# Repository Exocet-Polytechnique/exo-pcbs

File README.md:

# Cockpit
* 3 entrées GPIO (boutons)
* 3 sorties GPIO (DEL d'état)

#### Boutons

I = V/R

I = 3.3 / 10 000 = 0.33 mA

Utiliser un connecteur **JST ZH** (compact, facile à manipuler)

#### Del d'états

R = V / I = 3.3 - V<sub>D</sub> / 0.01

V<sub>D</sub> : Chute de tension directe (i.e. tension minimale requise pour que le courant commence à circuler à travers un composant électronique). Pour une DEL rouge ou verte, V<sub>D</sub> = 2 V.

I = 10 mA (Assez de courant pour faire briller une DEL)

R = 3.3 - 2 / 0.01 = 130 Ω

Utiliser un connecteur **JST GH** (plus compact, mais un peu compliqué à manipuler)

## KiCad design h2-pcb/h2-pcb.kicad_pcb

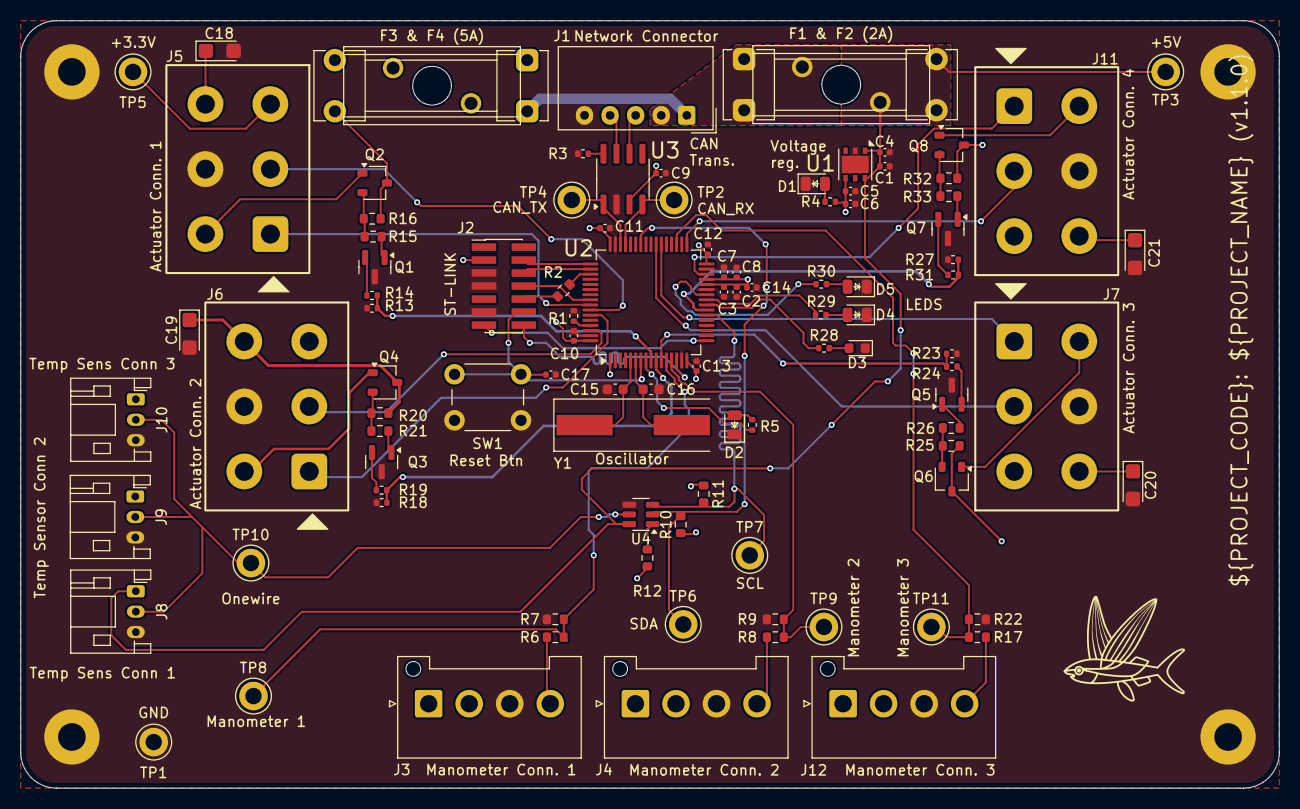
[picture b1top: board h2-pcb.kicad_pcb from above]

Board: 2 copper layers, 123.0 x 75.0 mm, 104 parts (0 on the bottom side), 69 nets.

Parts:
C1, C3, C6, C9, C10, C11, C12, C13, C17: 100n; C_0402_1005Metric
C2, C4, C5, C8: 1u; C_0402_1005Metric
C7: 10n; C_0402_1005Metric
C14: 4.7u; C_0402_1005Metric
C15, C16: 30p; C_0603_1608Metric
C18, C19, C20, C21: 10u; CP_EIA-3216-18_Kemet-A
D1, D4: GREEN; LED_0805_2012Metric_With_Annotations
D2, D5: YELLOW; LED_0805_2012Metric_With_Annotations
D3: RED; LED_0603_1608Metric
F1: 2A; Fuse_Holder_Littelfuse_01530008
F2: 2A; Fuseholder_Clip-5x20mm_Littelfuse_111_Lateral_P18.80x5.00mm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
F3: 5A; Fuse_Holder_Littelfuse_01530008
F4: 5A; Fuseholder_Clip-5x20mm_Littelfuse_111_Lateral_P18.80x5.00mm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
H1, H2, H3, H4: 2.7mm; MountingHole_2.7mm_Pad
J1: Network Connector; Molex_SPOX_5268-05A_1x05_P2.50mm_Horizontal
J2: STDC14; PinHeader_2x07_P1.27mm_Vertical_SMD
J3: Manometer Connector 1; JST_VH_B4P-VH-FB-B_1x04_P3.96mm_Vertical
J4: Manometer Connector 2; JST_VH_B4P-VH-FB-B_1x04_P3.96mm_Vertical
J5: Actuator Connector 1; TE_UNIVERSAL-MNL_6Pin_Horizontal_PCB_Header
J6: Actuator Connector 2; TE_UNIVERSAL-MNL_6Pin_Horizontal_PCB_Header
J7: Actuator Connector 3; TE_UNIVERSAL-MNL_6Pin_Horizontal_PCB_Header
J8: Temp Sensor Conn 1; JST_PH_S3B-PH-K_1x03_P2.00mm_Horizontal
J9: Temp Sensor Conn 2; JST_PH_S3B-PH-K_1x03_P2.00mm_Horizontal
J10: Temp Sensor Conn 3; JST_PH_S3B-PH-K_1x03_P2.00mm_Horizontal
J11: Actuator Connector 4; TE_UNIVERSAL-MNL_6Pin_Horizontal_PCB_Header
J12: Manometer Connector 3; JST_VH_B4P-VH-FB-B_1x04_P3.96mm_Vertical
Q1, Q3, Q5, Q7: NMOS; SOT-23
Q2, Q4, Q6, Q8: PMOS; SOT-23W
R1, R3, R13, R18, R23, R27: 10k; R_0402_1005Metric
R2: 47; R_0603_1608Metric
R4, R5, R28, R29, R30: 1k; R_0402_1005Metric
R6, R8, R17: 3.6k; R_0603_1608Metric
R7, R9, R10, R11, R12, R22: 6.8k; R_0603_1608Metric
R14, R19, R24, R31: 100; R_0402_1005Metric
R15, R21, R26, R33: 7.5k; R_0603_1608Metric
R16, R20, R25, R32: 4.7k; R_0603_1608Metric
SW1: SW_Push; SW_PUSH_6mm
TP1, TP2, TP3, TP4, TP5, TP6, TP7, TP8, TP9, TP10, TP11: TestPoint; TestPoint_Keystone_5005-5009_Compact
U1: LD39050PU33R; DFN-6-1EP_3x3mm_P0.95mm_EP1.7x2.6mm
U2: STM32G474RBT6; LQFP-64_10x10mm_P0.5mm
U3: SN65HVD230; SOIC-8_3.9x4.9mm_P1.27mm
U4: DS2484R; SOT-23-6
Y1: 8MHz; Crystal_SMD_HC49-SD

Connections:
+3.3V: C2.2, C3.2, C5.1, C6.1, C7.1, C8.1, C9.1, C10.1, C11.1, C12.1, C13.1, C14.1, J2.3 (VCC), J5.3, J6.3, J7.3, J11.3, R4.1, R10.1, R11.1, R12.1, TP5.1, U1.4 (V_{out}), U2.1 (VBAT), U2.16 (VDD), U2.28 (VREF+), U2.29 (VDDA), U2.32 (VDD), U2.48 (VDD), U2.64 (VDD), U3.3 (VCC)
+5V: C1.1, C4.1, F1.2, F2.2, J8.1, J9.1, J10.1, TP3.1, U1.1 (EN), U1.6 (V_{in}), U4.6 (V_{CC})
+24V: C18.1, C19.1, C20.1, C21.1, F3.2, F4.2, J3.1, J4.1, J5.6, J6.6, J7.6, J11.6, J12.1, Q2.3 (S), Q4.3 (S), Q6.3 (S), Q8.3 (S), R16.1, R20.1, R25.1, R32.1
/ACTUATOR_CTRL1: J5.4, Q2.1 (D)
/ACTUATOR_CTRL2: J6.4, Q4.1 (D)
/ACTUATOR_CTRL3: J7.4, Q6.1 (D)
/ACTUATOR_CTRL4: J11.4, Q8.1 (D)
/ACTUATOR_GPIO1: R13.1, R14.1, U2.9 (PC1)
/ACTUATOR_GPIO2: R18.1, R19.1, U2.10 (PC2)
/ACTUATOR_GPIO3: R23.1, R24.1, U2.11 (PC3)
/ACTUATOR_GPIO4: R27.1, R31.1, U2.23 (PC5)
/LED_1: R28.1, U2.24 (PB0)
/LED_2: R29.1, U2.25 (PB1)
/LED_3: R30.1, U2.26 (PB2)
/MANOMETER_1: R6.2, R7.1, TP8.1, U2.12 (ADC1_IN1)
/MANOMETER_2: R8.2, R9.1, TP9.1, U2.13 (ADC2_IN2)
/MANOMETER_3: R17.2, R22.1, TP11.1, U2.35 (ADC3_IN5)
/NC_1: J5.2, U2.58 (PB5)
/NC_2: J6.2, U2.62 (PB9)
/NC_3: J7.2, U2.39 (PC7)
/NC_4: J11.2, U2.33 (PB11)
/NO_1: J5.1, U2.57 (PB4)
/NO_2: J6.1, U2.59 (PB6)
/NO_3: J7.1, U2.38 (PC6)
/NO_4: J11.1, U2.30 (PB10)
/ONEWIRE: J8.2, J9.2, J10.2, TP10.1, U4.5 (IO)
/SCL_TEMP: R11.2, TP7.1, U2.22 (I2C2_SCL), U4.3 (SCL)
/SDA_TEMP: R10.2, TP6.1, U2.42 (I2C2_SDA), U4.2 (SDA)
/STM32 Base Layout/CAN_H: J1.4 (CAN_H), U3.7 (CANH)
/STM32 Base Layout/CAN_L: J1.3 (CAN_L), U3.6 (CANL)
/STM32 Base Layout/CAN_RX: TP2.1, U2.45 (FDCAN1_RX), U3.4 (R)
/STM32 Base Layout/CAN_TX: TP4.1, U2.46 (FDCAN1_TX), U3.1 (D)
/STM32 Base Layout/OSC_IN: C15.1, U2.5 (RCC_OSC_IN), Y1.1
/STM32 Base Layout/OSC_OUT: C16.1, U2.6 (RCC_OSC_OUT), Y1.2
/STM32 Base Layout/STATUS_LED: R5.1, U2.8 (PC0)
/STM32 Base Layout/T_JCLK/T_SWCLK: J2.6 (JCLK/SWCLK), U2.50 (SYS_JTCK-SWCLK)
/STM32 Base Layout/T_JTDI: J2.10 (JTDI/NC), R2.2
/STM32 Base Layout/T_JTDO/T_SWO: J2.8 (JTDO/SWO), U2.56 (SYS_JTDO-SWO)
/STM32 Base Layout/T_JTMS/T_SWDIO: J2.4 (JTMS/SWDIO), U2.49 (SYS_JTMS-SWDIO)
/STM32 Base Layout/T_NRST: C17.2, J2.12 (~RST), SW1.1, U2.7 (PG10)
/STM32 Base Layout/T_VCP_RX: J2.13 (VCP_RX), U2.17 (LPUART1_RX)
/STM32 Base Layout/T_VCP_TX: J2.14 (VCP_TX), U2.14 (LPUART1_TX)
GND: C1.2, C2.1, C3.1, C4.2, C5.2, C6.2, C7.2, C8.2, C9.2, C10.2, C11.2, C12.2, C13.2, C14.2, C15.2, C16.2, C17.1, C18.2, C19.2, C20.2, C21.2, D1.1 (K), D2.1 (K), D3.1 (K), D4.1 (K), D5.1 (K), H1.1, H2.1, H3.1, H4.1, J1.5 (GND), J2.5 (GND), J2.7 (GND), J2.11 (GNDDetect), J3.3, J4.3, J5.5, J6.5, J7.5, J8.3, J9.3, J10.3, J11.5, J12.3, Q1.3 (S), Q3.3 (S), Q5.3 (S), Q7.3 (S), R1.2, R3.2, R7.2, R9.2, R13.2, R18.2, R22.2, R23.2, R27.2, SW1.2, TP1.1, U1.2 (GND), U1.7 (GND), U2.15 (VSS), U2.27 (VSSA), U2.31 (VSS), U2.47 (VSS), U2.63 (VSS), U3.2 (GND), U4.4 (GND)
unnamed: D1.2 (A), R4.2
unnamed: D2.2 (A), R5.2
unnamed: D3.2 (A), R28.2
unnamed: D4.2 (A), R29.2
unnamed: D5.2 (A), R30.2
unnamed: F1.1, F2.1, J1.2 (+5V)
unnamed: F3.1, F4.1, J1.1 (+24V)
unnamed: J3.4, R6.1
unnamed: J4.4, R8.1
unnamed: J12.4, R17.1
unnamed: Q1.1 (D), R15.2
unnamed: Q1.2 (G), R14.2
unnamed: Q2.2 (G), R15.1, R16.2
unnamed: Q3.1 (D), R21.2
unnamed: Q3.2 (G), R19.2
unnamed: Q4.2 (G), R20.2, R21.1
unnamed: Q5.1 (D), R26.2
unnamed: Q5.2 (G), R24.2
unnamed: Q6.2 (G), R25.2, R26.1
unnamed: Q7.1 (D), R33.2
unnamed: Q7.2 (G), R31.2
unnamed: Q8.2 (G), R32.2, R33.1
unnamed: R2.1, U2.51 (SYS_JTDI)
unnamed: R1.1, U2.61 (PB8)
unnamed: R3.1, U3.8 (Rs)
unnamed: R12.2, U4.1 (~SLPZ)

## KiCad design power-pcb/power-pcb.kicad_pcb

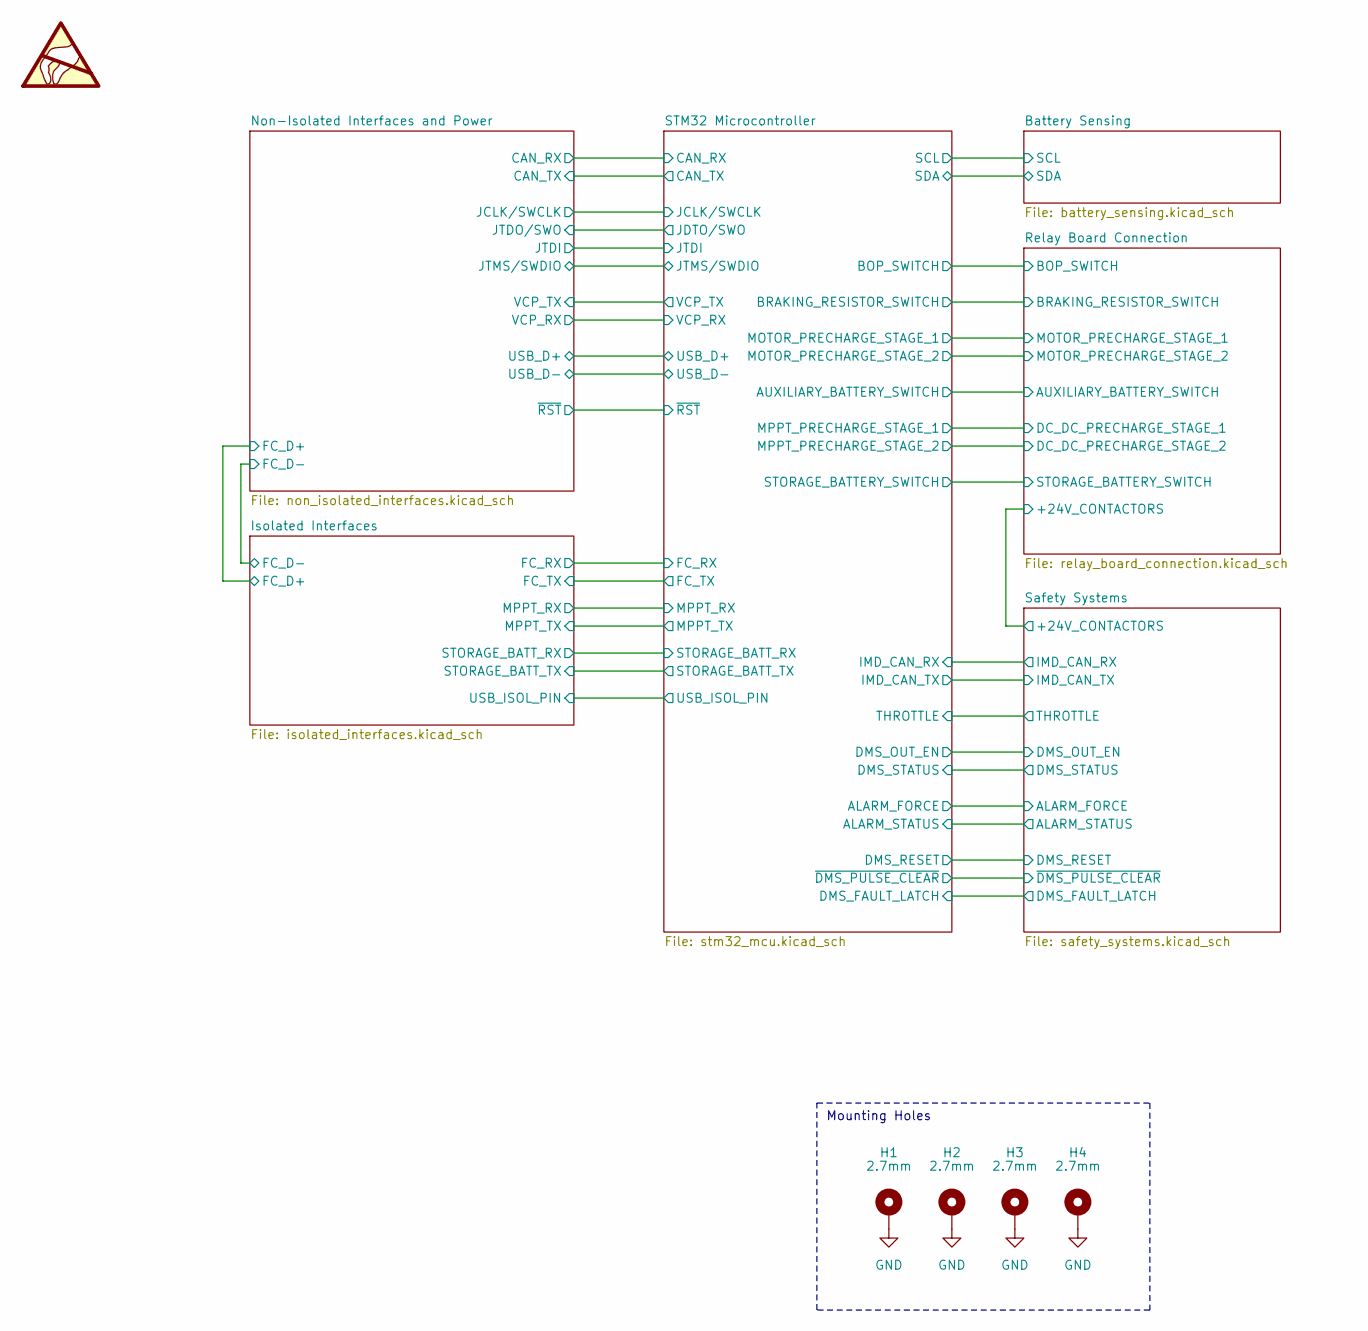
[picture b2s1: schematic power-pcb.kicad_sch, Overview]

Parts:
H1, H2, H3, H4: 2.7mm; MountingHole_2.7mm_Pad
SYM1: SYM_ESD_Large; ESD-Logo_8.9x8mm_SilkScreen

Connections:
GND: H1.1 (1_1), H2.1 (1_1), H3.1 (1_1), H4.1 (1_1); also elsewhere on the board

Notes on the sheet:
Mounting Holes

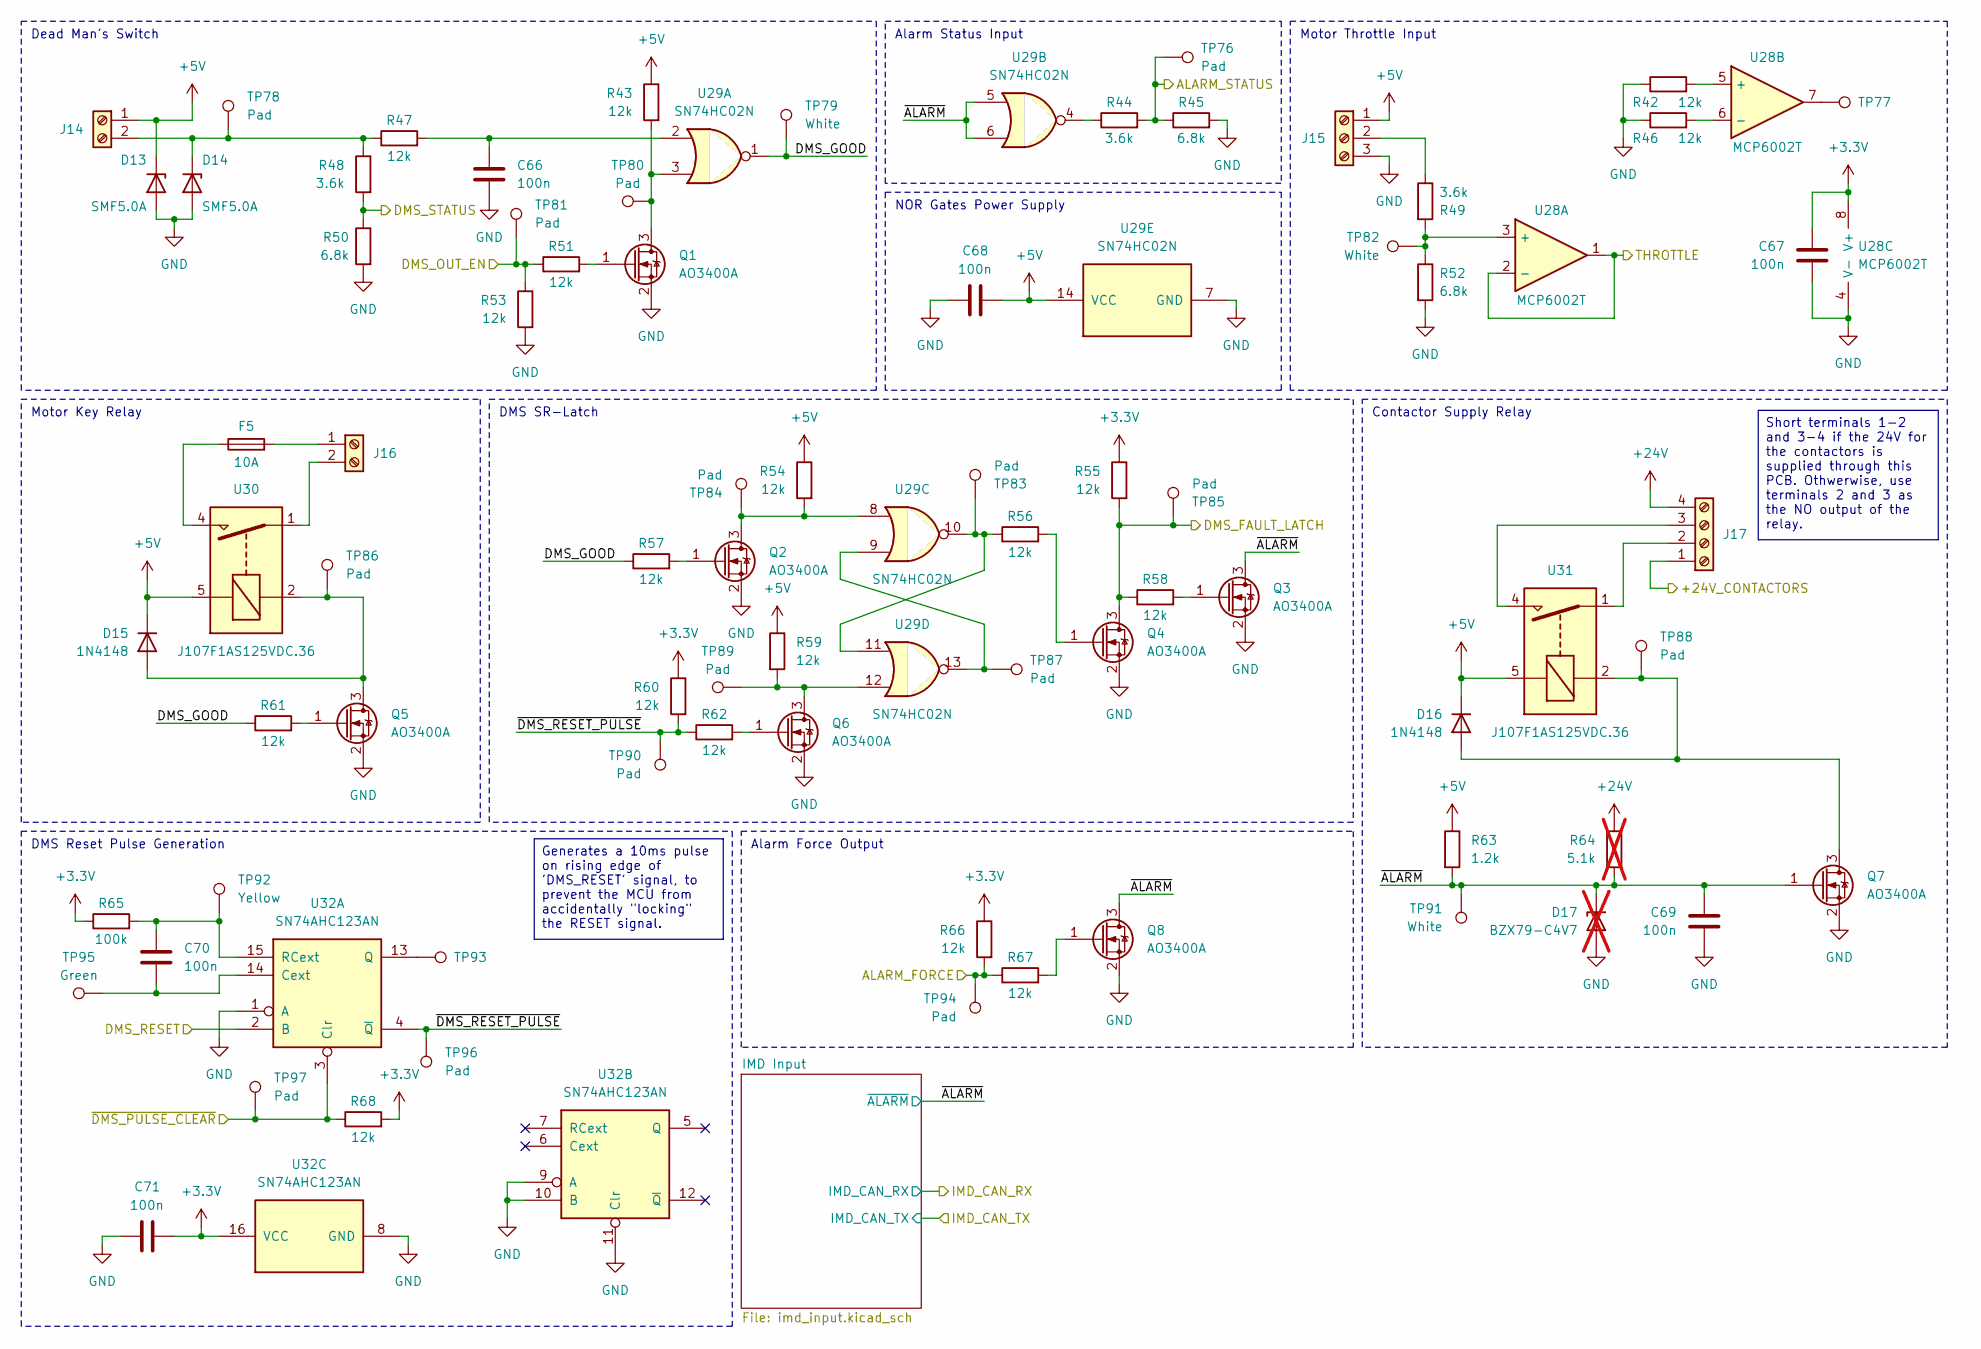
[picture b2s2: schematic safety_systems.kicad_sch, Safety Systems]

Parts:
C66, C67, C68, C69, C70, C71: 100n; C_0402_1005Metric_Pad0.74x0.62mm_HandSolder; JLCPCB C307331
D13, D14: SMF5.0A; D_SOD-123F; JLCPCB C19077497
D15, D16: 1N4148; D_DO-35_SOD27_P7.62mm_Horizontal; MPN 1N4148
D17: BZX79-C4V7; D_DO-35_SOD27_P7.62mm_Horizontal; MPN BZX79-C4V7,133; not fitted
F5: 10A; Fuseholder_Littelfuse_Combined; MPN 01110501Z
J14, J16: Screw_Terminal_01x02; Wuerth_Term_Blk_2pos_Side_Entry_5mm; MPN 691137710002
J15: Screw_Terminal_01x03; Wuerth_Term_Blk_3pos_Side_Entry_5mm; MPN 691137710003
J17: Screw_Terminal_01x04; Wuerth_Term_Blk_4pos_Side_Entry_5mm; MPN 691137710004
Q1, Q2, Q3, Q4, Q5, Q6, Q7, Q8: AO3400A; SOT-23_Handsoldering; MPN AO3400A; JLCPCB C20917
R42, R43, R46, R47, R51, R53, R54, R55, R56, R57, R58, R59, R60, R61, R62, R66, R67, R68: 12k; R_0402_1005Metric_Pad0.72x0.64mm_HandSolder; JLCPCB C25752
R44, R48, R49: 3.6k; R_0603_1608Metric_Pad0.98x0.95mm_HandSolder; JLCPCB C22980
R45, R50, R52: 6.8k; R_0603_1608Metric_Pad0.98x0.95mm_HandSolder; JLCPCB C23212
R63: 1.2k; R_0603_1608Metric_Pad0.98x0.95mm_HandSolder; JLCPCB C22765
R64: 5.1k; R_0402_1005Metric_Pad0.72x0.64mm_HandSolder; JLCPCB C25905; not fitted
R65: 100k; R_0603_1608Metric_Pad0.98x0.95mm_HandSolder; JLCPCB C25803
TP76, TP78, TP80, TP81, TP83, TP84, TP85, TP86, TP87, TP88, TP89, TP90, TP94, TP96, TP97: Pad; TestPoint_Pad_D1.5mm
TP77, TP93: Hole; TestPoint_THTPad_D2.0mm_Drill1.0mm
TP79, TP82, TP91: White; TestPoint_Keystone_5005-5009_Compact; MPN 5007
TP92: Yellow; TestPoint_Keystone_5005-5009_Compact; MPN 5009
TP95: Green; TestPoint_Keystone_5005-5009_Compact; MPN 5121
U28: MCP6002T; SOIC-8_3.9x4.9mm_P1.27mm; MPN MCP6002T-I/SN; JLCPCB C7377
U29: SN74HC02N; DIP-14_W7.62mm_LongPads; MPN SN74HC02N
U30, U31: J107F1AS125VDC.36; Relay_SPDT_Omron-G5LE-1; MPN J107F1AS125VDC.36
U32: SN74AHC123AN; DIP-16_W7.62mm_LongPads; MPN SN74AHC123AN

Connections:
+3.3V: C67.1, C71.2, R55.1, R60.1, R65.1, R66.1, R68.2, U28.8 (V+), U32.16 (VCC); also elsewhere on the board
+5V: C68.2, D13.1 (K), D15.1 (K), D16.1 (K), J14.1, J15.1, R43.1, R54.1, R59.1, R63.1, U29.14 (VCC), U30.5, U31.5; also elsewhere on the board
+24V: J17.4, R64.1; also elsewhere on the board
/Relay Board Connection/+24V_CONTACTORS: J17.1; also elsewhere on the board
/STM32 Microcontroller/ALARM_FORCE: R66.2, R67.1, TP94.1 (1_1); also elsewhere on the board
/STM32 Microcontroller/ALARM_STATUS: R44.2, R45.1, TP76.1 (1_1); also elsewhere on the board
/STM32 Microcontroller/DMS_FAULT_LATCH: Q4.3 (D), R55.2, R58.1, TP85.1 (1_1); also elsewhere on the board
/STM32 Microcontroller/DMS_OUT_EN: R51.1, R53.1, TP81.1 (1_1); also elsewhere on the board
/STM32 Microcontroller/DMS_RESET: U32.2 (B); also elsewhere on the board
/STM32 Microcontroller/DMS_STATUS: R48.2, R50.1; also elsewhere on the board
/STM32 Microcontroller/THROTTLE: U28.1, U28.2 (-); also elsewhere on the board
/STM32 Microcontroller/~DMS_PULSE_CLEAR: R68.1, TP97.1 (1_1), U32.3 (Clr); also elsewhere on the board
/Safety Systems/DMS_GOOD: R57.1, R61.1, TP79.1 (1_1), U29.1
/Safety Systems/~ALARM: C69.1, D17.1 (K), Q3.3 (D), Q7.1 (G), Q8.3 (D), R63.2, R64.2, TP91.1 (1_1), U29.5, U29.6; also elsewhere on the board
/Safety Systems/~DMS_RESET_PULSE: R60.2, R62.1, TP90.1 (1_1), TP96.1 (1_1), U32.4 (~Q)
GND: C66.2, C67.2, C68.1, C69.2, C71.1, D13.2 (A), D14.2 (A), D17.2 (A), J15.3, Q1.2 (S), Q2.2 (S), Q3.2 (S), Q4.2 (S), Q5.2 (S), Q6.2 (S), Q7.2 (S), Q8.2 (S), R42.1, R45.2, R46.1, R50.2, R52.2, R53.2, U28.4 (V-), U29.7 (GND), U32.1 (A), U32.8 (GND), U32.9 (A), U32.10 (B), U32.11 (Clr); also elsewhere on the board
unnamed: C66.1, R47.2, U29.2
unnamed: D14.1 (K), J14.2, R47.1, R48.1, TP78.1 (1_1)
unnamed: D15.2 (A), Q5.3 (D), TP86.1 (1_1), U30.2
unnamed: D16.2 (A), Q7.3 (D), TP88.1 (1_1), U31.2
unnamed: F5.1, U30.4
unnamed: J15.2, R49.1
unnamed: F5.2, J16.1
unnamed: J16.2, U30.1
unnamed: J17.2, U31.1
unnamed: J17.3, U31.4
unnamed: Q1.3 (D), R43.2, TP80.1 (1_1), U29.3
unnamed: Q1.1 (G), R51.2
unnamed: Q2.3 (D), R54.2, TP84.1 (1_1), U29.8
unnamed: Q2.1 (G), R57.2
unnamed: Q3.1 (G), R58.2
unnamed: Q4.1 (G), R56.2
unnamed: Q5.1 (G), R61.2
unnamed: Q6.3 (D), R59.2, TP89.1 (1_1), U29.12
unnamed: Q6.1 (G), R62.2
unnamed: Q8.1 (G), R67.2
unnamed: R44.1, U29.4
unnamed: R56.1, TP83.1 (1_1), U29.10, U29.11
unnamed: TP77.1 (1_1), U28.7
unnamed: TP87.1 (1_1), U29.9, U29.13
unnamed: R49.2, R52.1, TP82.1 (1_1), U28.3 (+)
unnamed: R42.2, U28.5 (+)
unnamed: R46.2, U28.6 (-)
unnamed: C70.2, TP95.1 (1_1), U32.14 (Cext)
unnamed: TP93.1 (1_1), U32.13 (Q)
unnamed: C70.1, R65.2, TP92.1 (1_1), U32.15 (RCext)

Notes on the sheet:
DMS SR-Latch
Motor Key Relay
DMS Reset Pulse Generation
Dead Man's Switch
Motor Throttle Input
NOR Gates Power Supply
Contactor Supply Relay
Alarm Status Input
Alarm Force Output
Short terminals 1-2 and 3-4 if the 24V for the contactors is supplied through this PCB. Othwerwise, use terminals 2 and 3 as the NO output of the relay.
Generates a 10ms pulse on rising edge of 'DMS_RESET' signal, to prevent the MCU from accidentally "locking" the RESET signal.

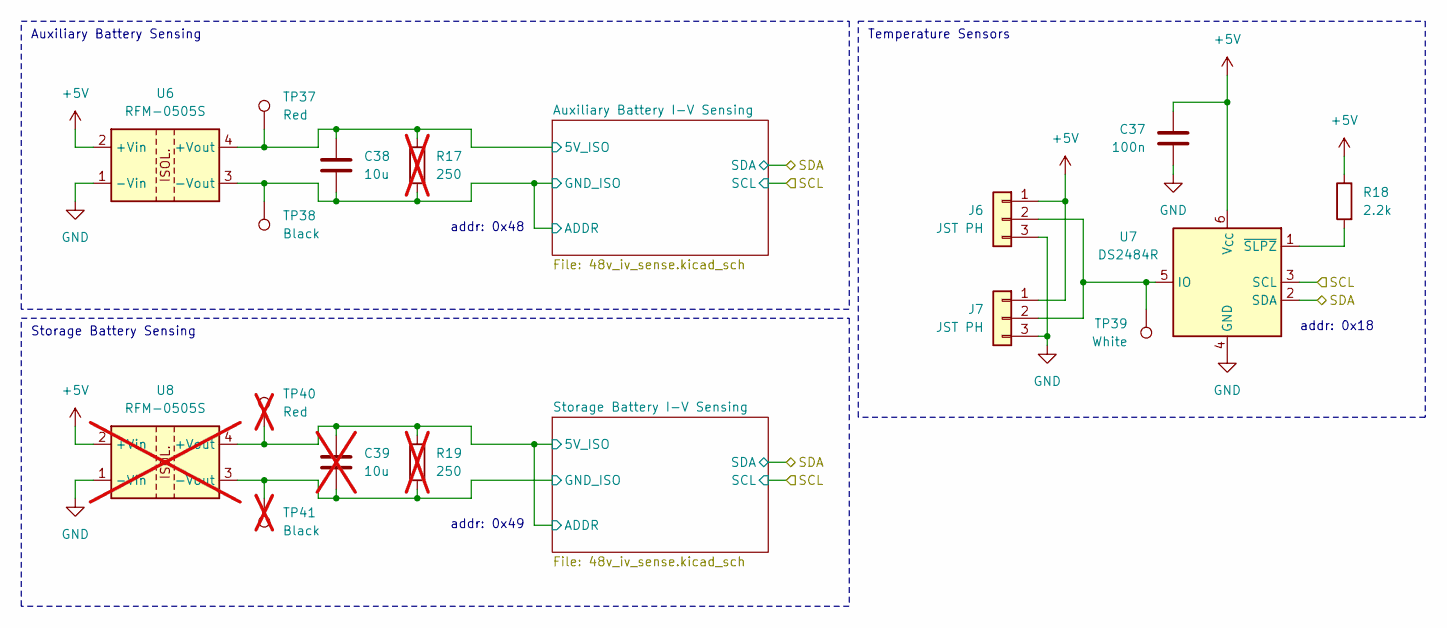
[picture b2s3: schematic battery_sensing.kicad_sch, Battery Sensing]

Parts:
C37: 100n; C_0402_1005Metric_Pad0.74x0.62mm_HandSolder; JLCPCB C307331
C38: 10u; C_1206_3216Metric_Pad1.33x1.80mm_HandSolder; JLCPCB C13585
C39: 10u; C_1206_3216Metric_Pad1.33x1.80mm_HandSolder; JLCPCB C13585; not fitted
J6, J7: JST PH; JST_PH_S3B-PH-K_1x03_P2.00mm_Horizontal; MPN S3B-PH-K-S
R17, R19: 250; R_Axial_DIN0309_L9.0mm_D3.2mm_P12.70mm_Horizontal; MPN MFR-25FTE52-270R; not fitted
R18: 2.2k; R_0603_1608Metric_Pad0.98x0.95mm_HandSolder; JLCPCB C4190
TP37: Red; TestPoint_Keystone_5005-5009_Compact; MPN 5005
TP38: Black; TestPoint_Keystone_5005-5009_Compact; MPN 5006
TP39: White; TestPoint_Keystone_5005-5009_Compact; MPN 5007
TP40: Red; TestPoint_Keystone_5005-5009_Compact; MPN 5005; not fitted
TP41: Black; TestPoint_Keystone_5005-5009_Compact; MPN 5006; not fitted
U6: RFM-0505S; RECOM_SIP-4; MPN RFM-0505S
U7: DS2484R; SOT-23-6; JLCPCB C124886
U8: RFM-0505S; RECOM_SIP-4; MPN RFM-0505S; not fitted

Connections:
+5V: C37.1, J6.1, J7.1, R18.1, U6.2 (+Vin), U7.6 (V_{CC}), U8.2 (+Vin); also elsewhere on the board
/Battery Sensing/Auxiliary Battery I-V Sensing/5V_ISO: C38.1, R17.1, TP37.1 (1_1), U6.4 (+Vout); also elsewhere on the board
/Battery Sensing/Auxiliary Battery I-V Sensing/ADDR: C38.2, R17.2, TP38.1 (1_1), U6.3 (-Vout); also elsewhere on the board
/Battery Sensing/SCL: U7.3 (SCL); also elsewhere on the board
/Battery Sensing/SDA: U7.2 (SDA); also elsewhere on the board
/Battery Sensing/Storage Battery I-V Sensing/5V_ISO: C39.1, R19.1, TP40.1 (1_1), U8.4 (+Vout); also elsewhere on the board
/Battery Sensing/Storage Battery I-V Sensing/GND_ISO: C39.2, R19.2, TP41.1 (1_1), U8.3 (-Vout); also elsewhere on the board
GND: C37.2, J6.3, J7.3, U6.1 (-Vin), U7.4 (GND), U8.1 (-Vin); also elsewhere on the board
unnamed: J6.2, J7.2, TP39.1 (1_1), U7.5 (IO)
unnamed: R18.2, U7.1 (~SLPZ)

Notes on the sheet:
Temperature Sensors
addr: 0x18
Auxiliary Battery Sensing
Storage Battery Sensing
addr: 0x49
addr: 0x48

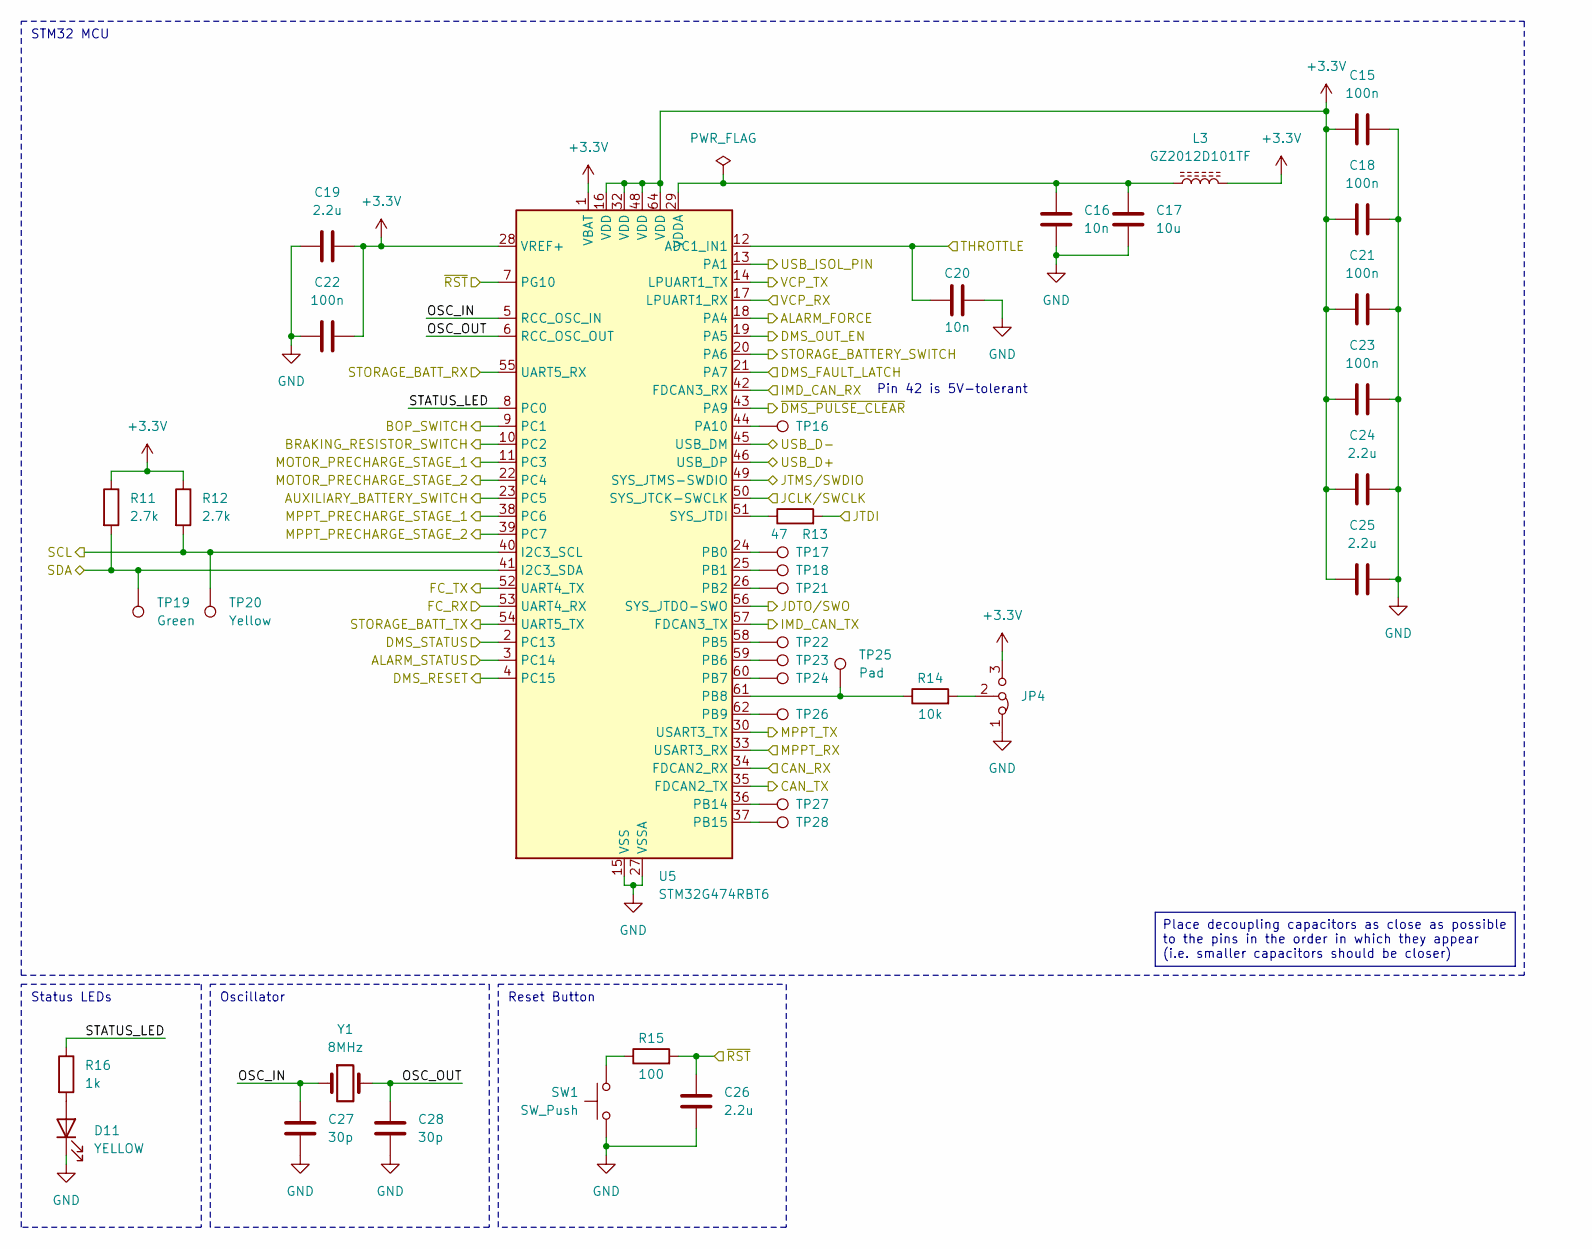
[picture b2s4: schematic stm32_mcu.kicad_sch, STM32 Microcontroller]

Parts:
C15, C18, C21, C22, C23: 100n; C_0402_1005Metric_Pad0.74x0.62mm_HandSolder; JLCPCB C307331
C16, C20: 10n; C_0402_1005Metric_Pad0.74x0.62mm_HandSolder; JLCPCB C15195
C17: 10u; C_1206_3216Metric_Pad1.33x1.80mm_HandSolder; JLCPCB C13585
C19, C24, C25, C26: 2.2u; C_0805_2012Metric_Pad1.18x1.45mm_HandSolder; JLCPCB C377773
C27, C28: 30p; C_0603_1608Metric_Pad1.08x0.95mm_HandSolder; JLCPCB C1658
D11: YELLOW; LED_0805_2012Metric_With_Annotations; JLCPCB C2296
JP4: Jumper_3_Bridged12; PinHeader_1x03_P2.54mm_Vertical; MPN PR20203VBNN
L3: GZ2012D101TF; L_0805_2012Metric_Pad1.05x1.20mm_HandSolder; JLCPCB C1015
R11, R12: 2.7k; R_0603_1608Metric_Pad0.98x0.95mm_HandSolder; JLCPCB C13167
R13: 47; R_0603_1608Metric_Pad0.98x0.95mm_HandSolder; JLCPCB C23182
R14: 10k; R_0805_2012Metric_Pad1.20x1.40mm_HandSolder; JLCPCB C17414
R15: 100; R_0603_1608Metric_Pad0.98x0.95mm_HandSolder; JLCPCB C22775
R16: 1k; R_0603_1608Metric_Pad0.98x0.95mm_HandSolder; JLCPCB C21190
SW1: SW_Push; SW_PUSH_6mm; MPN 1825910-6
TP16, TP17, TP18, TP21, TP22, TP23, TP24, TP26, TP27, TP28: Hole; TestPoint_THTPad_D2.0mm_Drill1.0mm
TP19: Green; TestPoint_Keystone_5005-5009_Compact; MPN 5121
TP20: Yellow; TestPoint_Keystone_5005-5009_Compact; MPN 5009
TP25: Pad; TestPoint_Pad_D1.5mm
U5: STM32G474RBT6; LQFP-64_10x10mm_P0.5mm; JLCPCB C529413
Y1: 8MHz; Crystal_SMD_HC49-SD; Part Name X49SM8MSD2SC; JLCPCB C12674

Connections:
+3.3V: C15.1, C18.1, C19.2, C21.1, C22.2, C23.1, C24.1, C25.1, JP4.3 (B), L3.2, R11.1, R12.1, U5.1 (VBAT), U5.16 (VDD), U5.28 (VREF+), U5.32 (VDD), U5.48 (VDD), U5.64 (VDD); also elsewhere on the board
/Battery Sensing/SCL: R12.2, TP20.1 (1_1), U5.40 (I2C3_SCL); also elsewhere on the board
/Battery Sensing/SDA: R11.2, TP19.1 (1_1), U5.41 (I2C3_SDA); also elsewhere on the board
/Isolated Interfaces/FC_RX: U5.53 (UART4_RX); also elsewhere on the board
/Isolated Interfaces/FC_TX: U5.52 (UART4_TX); also elsewhere on the board
/Isolated Interfaces/MPPT_RX: U5.33 (USART3_RX); also elsewhere on the board
/Isolated Interfaces/MPPT_TX: U5.30 (USART3_TX); also elsewhere on the board
/Isolated Interfaces/STORAGE_BATT_RX: U5.55 (UART5_RX); also elsewhere on the board
/Isolated Interfaces/STORAGE_BATT_TX: U5.54 (UART5_TX); also elsewhere on the board
/Isolated Interfaces/USB_ISOL_PIN: U5.13 (PA1); also elsewhere on the board
/Non-Isolated Interfaces and Power/CAN_RX: U5.34 (FDCAN2_RX); also elsewhere on the board
/Non-Isolated Interfaces and Power/CAN_TX: U5.35 (FDCAN2_TX); also elsewhere on the board
/Non-Isolated Interfaces and Power/JCLK/SWCLK: U5.50 (SYS_JTCK-SWCLK); also elsewhere on the board
/Non-Isolated Interfaces and Power/JTDI: R13.2; also elsewhere on the board
/Non-Isolated Interfaces and Power/JTDO/SWO: U5.56 (SYS_JTDO-SWO); also elsewhere on the board
/Non-Isolated Interfaces and Power/JTMS/SWDIO: U5.49 (SYS_JTMS-SWDIO); also elsewhere on the board
/Non-Isolated Interfaces and Power/USB_D+: U5.46 (USB_DP); also elsewhere on the board
/Non-Isolated Interfaces and Power/USB_D-: U5.45 (USB_DM); also elsewhere on the board
/Non-Isolated Interfaces and Power/VCP_RX: U5.17 (LPUART1_RX); also elsewhere on the board
/Non-Isolated Interfaces and Power/VCP_TX: U5.14 (LPUART1_TX); also elsewhere on the board
/Non-Isolated Interfaces and Power/~RST: C26.2, R15.2, U5.7 (PG10); also elsewhere on the board
/Relay Board Connection/AUXILIARY_BATTERY_SWITCH: U5.23 (PC5); also elsewhere on the board
/Relay Board Connection/BOP_SWITCH: U5.9 (PC1); also elsewhere on the board
/Relay Board Connection/BRAKING_RESISTOR_SWITCH: U5.10 (PC2); also elsewhere on the board
/Relay Board Connection/DC_DC_PRECHARGE_STAGE_1: U5.38 (PC6); also elsewhere on the board
/Relay Board Connection/DC_DC_PRECHARGE_STAGE_2: U5.39 (PC7); also elsewhere on the board
/Relay Board Connection/MOTOR_PRECHARGE_STAGE_1: U5.11 (PC3); also elsewhere on the board
/Relay Board Connection/MOTOR_PRECHARGE_STAGE_2: U5.22 (PC4); also elsewhere on the board
/Relay Board Connection/STORAGE_BATTERY_SWITCH: U5.20 (PA6); also elsewhere on the board
/STM32 Microcontroller/ALARM_FORCE: U5.18 (PA4); also elsewhere on the board
/STM32 Microcontroller/ALARM_STATUS: U5.3 (PC14); also elsewhere on the board
/STM32 Microcontroller/DMS_FAULT_LATCH: U5.21 (PA7); also elsewhere on the board
/STM32 Microcontroller/DMS_OUT_EN: U5.19 (PA5); also elsewhere on the board
/STM32 Microcontroller/DMS_RESET: U5.4 (PC15); also elsewhere on the board
/STM32 Microcontroller/DMS_STATUS: U5.2 (PC13); also elsewhere on the board
/STM32 Microcontroller/IMD_CAN_RX: U5.42 (FDCAN3_RX); also elsewhere on the board
/STM32 Microcontroller/IMD_CAN_TX: U5.57 (FDCAN3_TX); also elsewhere on the board
/STM32 Microcontroller/OSC_IN: C27.1, U5.5 (RCC_OSC_IN), Y1.1
/STM32 Microcontroller/OSC_OUT: C28.1, U5.6 (RCC_OSC_OUT), Y1.2
/STM32 Microcontroller/STATUS_LED: R16.1, U5.8 (PC0)
/STM32 Microcontroller/THROTTLE: C20.1, U5.12 (ADC1_IN1); also elsewhere on the board
/STM32 Microcontroller/~DMS_PULSE_CLEAR: U5.43 (PA9); also elsewhere on the board
GND: C15.2, C16.1, C17.1, C18.2, C19.1, C20.2, C21.2, C22.1, C23.2, C24.2, C25.2, C26.1, C27.2, C28.2, D11.1 (K), JP4.1 (A), SW1.2, U5.15 (VSS), U5.27 (VSSA), U5.31 (VSS), U5.47 (VSS), U5.63 (VSS); also elsewhere on the board
unnamed: D11.2 (A), R16.2
unnamed: JP4.2 (C), R14.2
unnamed: R15.1, SW1.1
unnamed: TP16.1 (1_1), U5.44 (PA10)
unnamed: R13.1, U5.51 (SYS_JTDI)
unnamed: TP17.1 (1_1), U5.24 (PB0)
unnamed: TP18.1 (1_1), U5.25 (PB1)
unnamed: TP21.1 (1_1), U5.26 (PB2)
unnamed: TP22.1 (1_1), U5.58 (PB5)
unnamed: TP23.1 (1_1), U5.59 (PB6)
unnamed: TP24.1 (1_1), U5.60 (PB7)
unnamed: R14.1, TP25.1 (1_1), U5.61 (PB8)
unnamed: TP26.1 (1_1), U5.62 (PB9)
unnamed: TP27.1 (1_1), U5.36 (PB14)
unnamed: TP28.1 (1_1), U5.37 (PB15)
unnamed: C16.2, C17.2, L3.1, U5.29 (VDDA)

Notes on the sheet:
Oscillator
Reset Button
Pin 42 is 5V-tolerant
Status LEDs
STM32 MCU
Place decoupling capacitors as close as possible to the pins in the order in which they appear (i.e. smaller capacitors should be closer)

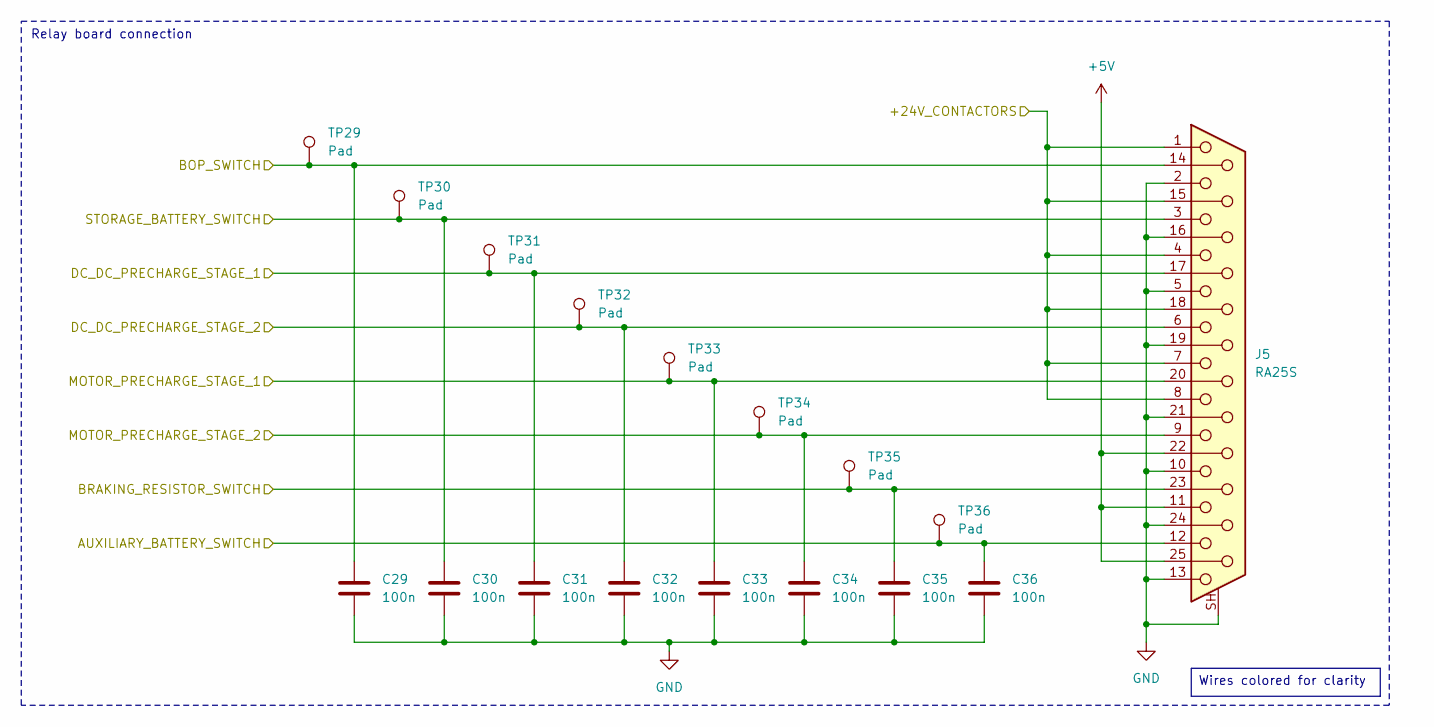
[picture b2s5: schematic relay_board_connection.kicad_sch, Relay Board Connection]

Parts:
C29, C30, C31, C32, C33, C34, C35, C36: 100n; C_0402_1005Metric_Pad0.74x0.62mm_HandSolder; JLCPCB C307331
J5: RA25S; DSUB-25_Socket_Horizontal_P2.77x2.84mm_EdgePinOffset7.70mm_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; MPN A-DF 25 A/KG-T2S
TP29, TP30, TP31, TP32, TP33, TP34, TP35, TP36: Pad; TestPoint_Pad_D1.5mm

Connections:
+5V: J5.11, J5.22, J5.25; also elsewhere on the board
/Relay Board Connection/+24V_CONTACTORS: J5.1, J5.4, J5.7, J5.8, J5.15, J5.18; also elsewhere on the board
/Relay Board Connection/AUXILIARY_BATTERY_SWITCH: C36.1, J5.12, TP36.1 (1_1); also elsewhere on the board
/Relay Board Connection/BOP_SWITCH: C29.1, J5.14, TP29.1 (1_1); also elsewhere on the board
/Relay Board Connection/BRAKING_RESISTOR_SWITCH: C35.1, J5.23, TP35.1 (1_1); also elsewhere on the board
/Relay Board Connection/DC_DC_PRECHARGE_STAGE_1: C31.1, J5.17, TP31.1 (1_1); also elsewhere on the board
/Relay Board Connection/DC_DC_PRECHARGE_STAGE_2: C32.1, J5.6, TP32.1 (1_1); also elsewhere on the board
/Relay Board Connection/MOTOR_PRECHARGE_STAGE_1: C33.1, J5.20, TP33.1 (1_1); also elsewhere on the board
/Relay Board Connection/MOTOR_PRECHARGE_STAGE_2: C34.1, J5.9, TP34.1 (1_1); also elsewhere on the board
/Relay Board Connection/STORAGE_BATTERY_SWITCH: C30.1, J5.3, TP30.1 (1_1); also elsewhere on the board
GND: C29.2, C30.2, C31.2, C32.2, C33.2, C34.2, C35.2, C36.2, J5.2, J5.5, J5.10, J5.13, J5.16, J5.19, J5.21, J5.24, J5.SH (PAD); also elsewhere on the board

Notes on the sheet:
Relay board connection
Wires colored for clarity
